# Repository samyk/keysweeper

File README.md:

**KEYSWEEPER // SIGINT // SAMY.PL // REL TO ALL // APPLIED HACKING**

# [KeySweeper](http://samy.pl/keysweeper/)

**[KeySweeper](http://samy.pl/keysweeper)** is a stealthy Arduino-based device, camouflaged as a functioning USB wall charger, that wirelessly and passively sniffs, decrypts, logs and reports back (over GSM) all keystrokes from any Microsoft wireless keyboard in the vicinity.

All keystrokes are logged online and locally. SMS alerts are sent upon trigger words, usernames or URLs, exposing passwords. If unplugged, KeySweeper continues to operate using its internal battery and auto-recharges upon repowering. A web based tool allows live keystroke monitoring.

**Live demonstration** and full details available in the video:

-----

**Point of Contact:** [@SamyKamkar](https://twitter.com/samykamkar) // <code@samy.pl> // <http://samy.pl>

**Released:** January 12, 2015

**Source code / schematic:** [https://github.com/samyk/keysweeper](https://github.com/samyk/keysweeper)

**Unit Cost:** $10 - 80 depending on operation

**Status:** Operational, open source, open hardware, declassified.

-----

# (U) Capabilities

**[KeySweeper](http://samy.pl/keysweeper)** is a stealthy Arduino-based device, camouflaged as a functioning USB wall charger, that wirelessly and passively sniffs, decrypts, logs and reports back all keystrokes from any Microsoft wireless keyboards (which use a proprietary 2.4GHz RF protocol) in the area.

Keystrokes are sent back to the KeySweeper operator over the Internet via an optional GSM chip, or can be stored on a flash chip and delivered wirelessly when a secondary KeySweeper device comes within wireless range of the target KeySweeper. A web based tool allows live keystroke monitoring.

KeySweeper has the capability to send SMS alerts upon certain keystrokes being typed, e.g. "www.bank.com". If KeySweeper is removed from AC power, it appears to shut off, however it continues to operate covertly using an internal battery that is automatically recharged upon reconnecting to AC power.

KeySweeper extends the work of Travis Goodspeed on the [goodfet.nrf](http://travisgoodspeed.blogspot.co.uk/2011/02/promiscuity-is-nrf24l01s-duty.html) project and of Thorsten Schröder and Max Moser of the [KeyKeriki v2.0](http://www.remote-exploit.org/?page_id=602) project.

-----

# (U) Hardware

### Arduino / Teensy microcontroller
**$3 - 30**: An [Arduino](http://arduino.cc/en/Main/ArduinoBoardProMini) or [Teensy](https://www.pjrc.com/teensy/) microcontroller can be used. In my build, I use an 3.3v Arduino Pro Mini due to its very thin profile.

### nRF24L01+ 2.4GHz RF Chip
**$1**: I use a $1 nRF24L01+ RF chip which communicates using GFSK over 2.4GHz. More details are available below, and these chips can be purchased for as low as $1 on eBay. These chips can only communicate using proprietary protocols, and are not meant for sniffing, however we will see below they can be used in clever ways to promiscuously sniff.

### AC USB Charger
**$6**: I use an inexpensive [AC USB charger](https://www.adafruit.com/products/501) (rectifier) which converts AC power to 5v DC, and this one I link to happens to have a screw which makes it easy to open (I've destroyed a few others in the process of opening). If using the GSM version of KeySweeper, I actually use two USB chargers -- the internals of a small charger (similar to that of an iPhone charger), and the external case from a larger USB charger.

### SPI Serial Flash Chip
**OPTIONAL ($2)**: An optional [SPI Serial Flash chip](https://www.adafruit.com/product/1564) can be used to store keystrokes on. If you use the FONA GSM board below, this is not necessary as keystrokes can be stored through the internet live, however if you wish to have a lower cost option, you can store keystrokes onto this chip within KeySweeper, and obtain the keystrokes later by getting within 2.4GHz wireless range of the device with a secondary device which will siphon the keystrokes from it.

Most microcontrollers have very limited memory or EEPROM to store data on, thus the advantage of having a flash chip to store these keystrokes on.

### Adafruit FONA
**OPTIONAL ($45)**: Adafruit has created a board called the [FONA](https://www.adafruit.com/products/1963) which allows you to use a 2G SIM card to send/receive SMS's, phone calls, and use the Internet directly from the device.

Using this, no flash chip is necessary as keystrokes are immediately sent to a backend server for proper data collection. Additionally, if specific keywords are ever typed by the target keyboards, an SMS message can be sent to a specified number to alert the operative of the fact.

### SIM Card
**OPTIONAL ($3, only if using FONA)**: The FONA requires a mini-SIM card (not a micro-SIM). I use a T-Mobile prepaid SIM card. I suggest use of T-Mobile as they support 2G, where most other carriers have or are deprecating their 2G network, and the FONA only supports 2G for Internet. Make sure you get the right size of SIM card -- more details on [FONA SIM requirements here](https://learn.adafruit.com/adafruit-fona-mini-gsm-gprs-cellular-phone-module/obtaining-a-sim).

### 3.7V Lithium-Ion (LiOn or LiPo) Battery
**OPTIONAL ($5 and up, only if using FONA)**: The FONA provides on-board LiPo/LiOn battery recharging, and while KeySweeper is connected to AC power, the battery will be kept charged, but is required nonetheless. Additionally, KeySweeper continues to operate covertly from battery power when pulled from AC power, and begins to recharge upon reconnecting to AC power.

-----

# (U) Software

### KeySweeper
KeySweeper's source code can be obtained in entirety from my github: <https://github.com/samyk/keysweeper>

There are multiple parts to KeySweeper. The primary code is installed on the microcontroller, while a web based backend using [jQuery](http://jquery.com/) and [PHP](http://php.net/) logs all keystrokes and provides a web interface for live monitoring of the target keyboards.

KeySweeper also needs the following files from [maniacbug's RF24 library](https://github.com/maniacbug/RF24):
* `RF24.h`
* `nRF24L01.h`
* `RF24_config.h`

Just copy the files into the `keysweeper_mcu_src` directory. You also have to change the `#include` statement in the `RF24.h` file from `#include <RF24_config.h>` to `#include "RF24_config.h"`.
 
### Adafruit FONA library
You should use [my version of the Adafruit FONA library](https://github.com/samyk/Adafruit_FONA_Library) as I include an additional option that allows the FONA to let us know when there's a new text message. In the original library, you must constantly poll to see if there are more text messages than you expect, however with my version you can enable an option `fona.setSMSInterrupt(1)` which causes the RI (Ring Interrupt) pin to pull low for a moment upon new SMS messages.

### jQuery Terminal
I've created a backend tool that allows you to monitor keyboards live through a web page. The [jQuery Terminal](http://terminal.jcubic.pl/) plugin makes it look cooler.

### jQuery UI Virtual Keyboard
[jQuery UI Virtual Keyboard](https://github.com/Mottie/Keyboard) continues to make the KeySweeper live spy interface tool look cool, showing keys on the virtual keyboard get pressed when the user actually presses keys.

-----

# (U) Determining Keyboard Wireless Protocol

Upon obtaining a Microsoft wireless keyboard, if it's in our possession, we can refer to the back to inspect the FCC ID. On my keyboard, the FCC ID (which is required by all devices using radio frequencies in the US) is **C3K1455**, which we can easily search on the [FCC's website](http://fccid.net/number.php?fcc=C3K1455&id=451957#axzz3NptwlcmB).

Immediately we discover the keyboard communicates on **2403 - 2480MHz** based on the [FCC report](http://fccid.net/number.php?fcc=C3K1455&id=451957#axzz3NptwlcmB).

Now that I know this is a 2.4GHz device, I assume it's either operating using a common 2.4GHz protocol such as wi-fi, bluetooth, zigbee, or others, or it's operating using a proprietary protocol. Due to the fact that the device came with its own USB dongle (with its own [FCC ID, C3K1461](http://fccid.net/number.php?fcc=C3K1461&id=247815#axzz3NptwlcmB)), it's more than likely a proprietary 2.4GHz signal.

Because it's likely proprietary 2.4GHz, we need to now use some method of 2.4GHz sniffing. Wifi sniffers will not help as this isn't 802.11 (such as what we used in [SkyJack](http://samy.pl/skyjack/)), and RTL-SDR by itself won't help as it caps out around 2.2GHz unless additionally using an RF down converter (we used RTL-SDR in [Digital Ding Dong Ditch](http://samy.pl/dingdong/)), so I immediately want to use [HackRF](https://greatscottgadgets.com/hackrf/), a powerful and inexpensive software defined radio, however while it's extremely powerful for its price, we may be able to get away with more inexpensive hardware.

Based off previous experience, my assumption is the keyboard is using something like a [Nordic nRF24L01+](https://www.nordicsemi.com/eng/Products/2.4GHz-RF/nRF24L01P), a [TI CC2500](http://www.ti.com/product/cc2500), or [Cypress CYRF6936](http://www.cypress.com/?rID=14284), but we won't know for sure without further inspection.

After pulling the screws from the keyboard and opening it up, we see a single chip responsible for everything. It's labeled **NRF 24LE1H**, which sounds a lot like nRF24L01 (n=[Nordic Semiconductor](https://www.nordicsemi.com/), RF=Radio Frequency, 24=2.4GHz)! We quickly find the [nRF24LE1](http://www.nordicsemi.com/eng/Products/2.4GHz-RF/nRF24LE1) chip with a search and see that it in fact has the nRF24L01+ RF chip integrated with a CPU (System-on-Chip/SoC), and a quick search on eBay shows the nRF24L01+ can be shipped to us for under $1.

	The nRF24LE1 integrates an nRF24L01+ 2.4GHz RF transceiver core, enhanced 16MHz 8-bit 8051 compatible CPU, 1kB + 256B RAM, 16kB embedded Flash, and a wide range of system peripherals

Looking at the [nRF24L01+ datasheet](https://www.sparkfun.com/datasheets/Components/SMD/nRF24L01Pluss_Preliminary_Product_Specification_v1_0.pdf), we see this is a 2.4GHz RF chip that operates at either 250kbps/1Mbps/2Mbps, uses GFSK ([Gaussian frequency-shift keying modulation](http://en.wikipedia.org/wiki/Gaussian_frequency-shift_keying) is a digital frequency modulation/FM), and unfortunately lacks any legitimate promiscuous or direct mode for sniffing...or does it?

-----

# (U) Sniffing Proprietary 2.4GHz Signals

While I would normally pull out something like a HackRF or RTL-SDR with digital down converter (to get 2.4GHz into RTL-SDR range), it would be really nice if we could sniff with more inexpensive hardware, as ultimately I want to package everything up into a device that can be left in the field.

After a basic search, an amazing page came up from [Travis Goodspeed](http://travisgoodspeed.blogspot.com/2011/02/promiscuity-is-nrf24l01s-duty.html), where he not only sniffs a similar keyboard (Microsoft Comfort Desktop 5000), but he also demonstrates how to turn the nRF24L01+ into a 2.4GHz sniffer using his [GoodFET](http://goodfet.sourceforge.net/) device, and a host computer with the [goodfet.nrf](http://goodfet.sourceforge.net/clients/goodfetnrf/) python application.

Travis found that sniffing with the device is traditionally difficult because not only must you specify the channel (frequency) to listen to, you must specify a MAC address to listen on. The nRF chip will only deliver packets sent to that specific MAC address. Additionally, the nRF chip  won't tell you the MAC address since you already specified it (it's assumed to be in one of our `RX_ADDR_P[0-5]` pipes, found in the datasheet.)

However when specifying the length of the MAC, Travis found there is one option which is considered "illegal" in the datasheet (`SETUP_AW, 0x03 set to 00`), but actually sets the MAC to 2 bytes! Also, by setting the MAC to data that would typically be found in the preamble (`0x00AA or 0x0055, in binary 0000000010101010 or 0000000001010101`), we can fool the device into giving us the packet early, providing a full MAC address to us in the data portion! Read his [great write-up](http://travisgoodspeed.blogspot.com/2011/02/promiscuity-is-nrf24l01s-duty.html) for all the details.

-----

# (U) Increasing Speed and Portability

Now while we can use a GoodFET, computer and nRF24L01+ for sniffing during testing, we ultimately want this to be on an inexpensive and embedded device. We can take some of Travis' great work in Python and port it over to embedded C so that we can load it onto a microcontroller rather than requiring a computer+GoodFET.

Additionally, we implement a few improvements. Goodfet.nrf provides a method of scanning for devices by performing the following:

* start at frequency 2400MHz
* set datarate to 1Mbps and MAC to 0x00AA, listen for 10 seconds
* set datarate to 2Mbps and MAC to 0x00AA, listen for 10 seconds
* set datarate to 1Mbps and MAC to 0x0055, listen for 10 seconds
* set datarate to 2Mbps and MAC to 0x0055, listen for 10 seconds
* increment frequency and start over, and once we hit 2528MHz, reset to 2400 (128 frequencies)
* upon seeing a potential keyboard, we require at least four packets to meet a threshold to be sure it's a legitimate packet as get many false positives

This means to scan the full range of frequencies, it takes ~85 minutes and at least several keystrokes must be pressed while we're sniffing within the correct 10 second period. After going over Travis' research and keyboard, the [KeyKeriki](http://www.remote-exploit.org/articles/keykeriki_v2_0__8211_2_4ghz/) research and keyboard, and my own keyboard, we can implement a few improvements:

* if you recall from the FCC, we're only using 2403 - 2480MHz for these keyboards, reducing our 128 possible frequencies down to 78 (about 40% reduction in scanning)
* all keyboards use 2Mbps, cutting our search in half
* after inspecting more keyboards, I found that all Microsoft keyboards begin with 0xCD as the MAC, which tells us that our preamble will always be `0xAA (10101010)` because the preamble of 0xAA is always followed by a 1 bit (`0xCD is 11001101`) in order to keep the bits alternating, cutting our search in half
* because we know the first byte of our MAC (0xCD), and we also know certain packets to look for, we simply detect only those packets which means we only ever need to see a single packet to be confident that it is in fact a keyboard
* we reduce the scan per frequency to 500ms, causing our scan to take under 40 seconds to complete one full sweep

-----

# (U) Decrypting Keystrokes

Thorsten Schröder and Max Moser presented a great device, the [KeyKeriki](http://www.remote-exploit.org/articles/keykeriki_v2_0__8211_2_4ghz/), capable of sniffing Microsoft keyboards and have fully reverse engineered the decryption process and produced a device for doing so. However Travis points out that their device requires two radios and a high-end microcontroller to capture and parse packets at the 2Mbps speed the keyboards communicate at. Travis' project is great as well, however requires a host computer and will be too large for our covert implementation. We improve upon these designs in this scenario by requiring only an inexpensive radio and microcontroller, both low power and very small, no computer or fancy radios required.

Thorsten and Max discovered the keystrokes are simply encrypted (xor'd) with the MAC address in [ECB mode](http://en.wikipedia.org/wiki/Block_cipher_mode_of_operation#Electronic_codebook_.28ECB.29), which we are able to sniff after using Travis' method of abusing the nRF24L01+ to both sniff and reveal MAC addresses. This "encryption" is the equivalent of taking a deck of cards, cutting it once, and calling it shuffled. 

After further investigation, I found that since we now know all Microsoft keyboards begin with 0xCD as the MAC address, the actual keystroke (in orange below) happens to be aligned with the first byte of the MAC address (0xCD). This means **even if we do not know the MAC address, we can decrypt the keystroke**, as the alignment will never change, and 0xCD is always the first byte of the MAC.

An additional discovery is that since the length of the encryption portion of the packet is 11 bytes, the MAC is 5 bytes, and the CRC is each byte xor'd with another (before encryption), something interesting happens. Since the MAC is xor'd twice, we can also calculate the checksum without knowing the MAC address. This is because the MAC address is in there in full twice, and xoring any number by itself (or xor the MAC with the MAC) cancels itself out. The 11th byte is the first byte of the MAC again, which we always know is 0xCD. This allows us to perform other attacks, such as altering the keystroke and CRC, again without knowing the MAC address. I will present this and some other fun demonstrations in a future project.

A page from the KeyKeriki presentation demonstrates the decryption process:

* Device type 0x0A = keyboard, 0x08 = mouse
* Packet type 0x78 = keystroke, 0x38 = idle (key is held down)
* Model type 0x06 = keyboard? This is the same HID code for a keyboard
* HID code 0x05 = letter 'b' (described in section 7 [here](http://www.freebsddiary.org/APC/usb_hid_usages.php))

Our decryption method, implemented in the KeySweeper source code:

```
// decrypt those keyboard packets!
void decrypt(uint8_t* pkt)
{
  // our encryption key is the 5-byte MAC address and
  // starts 4 bytes in (4-byte header is unencrypted)
  for (int i = 4; i < 15; i++)
    pkt[i] ^= mac >> (((i - 4) % 5) * 8) & 0xFF;
}
```

-----

# (U) Building / Usurping a USB Charger

**WARNING: Devices which connect to AC mains are using high-voltage power, and the device we are creating which connects to AC is not safe, nor does it meet typical electrical safety standards. This is a dangerous device and if used or built improperly, can kill, cause fire, or other severe damage. Do not build an AC-powered device unless you know what you're doing. If you wish to continue building this device but without AC power, simply use a battery or power the device from USB directly to safely follow along.**

KeySweeper uses extremely low-power and low profile hardware to remain as covert as possible. KeySweeper can be operated from a battery, or from ~3-20V DC power. Because we wish to keep KeySweeper powered at all times, we stealthily install it inside of an innocent wall USB charger which we expect to be always plugged in.

In the case that the USB charger is unplugged, KeySweeper stealthily continues its operation using its (optional) internal battery. The moment KeySweeper is plugged back in, it switches back over to using AC power, and simultaneously recharges the battery.

If you are simply building KeySweeper **without** the GSM board, you can fit everything in a typical AC USB wall charger. I suggest looking for one that has a screw holding it together, as most others are sealed shut and requires destruction of some part of the device in order to open it.

If you decide to use the GSM board, I found it would not fit in this type of USB charger along with the rest of the electronics. However, I discovered that by opening a smaller USB charger (similar to the iPhone USB chargers), we find a much smaller rectifier (AC->DC) and step-down convertor (high voltage->5V) that allows **all** of our electronics to fit into the larger USB charger. 

My friend Dana lent me her doll soldering iron. I don't quite understand what she uses it for, but it's a soldering iron with an attachable razor. This is great for cutting through plastic, and dolls, I presume. She took the iron back as soon as I explained what the device would do. Apparently she does not support this, though I'm not sure why. I'm sure I'll find out after I sniff more keystrokes from her keyboard.

**WARNING: Again, because we are dealing with AC power, this is very dangerous. Do not open/rewire an AC powered device unless you know what you're doing.** You can still build KeySweeper by simply powering everything from a USB charger, port or battery without modifying an AC-based device.

It's also important to wire up our Arduino via the RAW port to the 5v USB power with correct polarity (negative to GND, positive to RAW). In this case, I'm using a 3.3v Arduino Pro Mini. The RAW port takes in unregulated voltage between 3.35-12v and uses an onboard voltage regulator to bring it down to 3.3v. Note that our nRF24L01+ chip requires 1.9-3.6v, so giving it 5v is **too much!** Additionally, if you're using an SPI chip such as the [SST25VF016B](http://ww1.microchip.com/downloads/en/DeviceDoc/S71271_04.pdf), it requires 2.7-3.6v, so again using 5v is **too much!** Be sure to use the regulated 3.3v off of the Arduino (from the VCC pin on a 3.3v Arduino, or the 3V3 pin on a 5v Arduino.) 

*note: the USB board pictured next to the multimeter is the original before I had decided to swap it out with a smaller one to fit in the GSM board as well*

After grabbing all of our hardware, we can see it all fits with space in our charger (before wiring):

For fun, I tied the charger's LED to pin 6 on the Arduino and while the LED appears to behave the same, I actually have it flash upon sniffing keystrokes. This will likely blow your cover, but is really fun to watch. I also ensure the LED turns off when power to AC is lost, even if the rest of the device continues to operate from the internal battery.

We also want to make sure we leave the rest of the USB charger operational so that other devices can continue to get power from the USB charger.

-----

# (U) Optional Secondary KeySweeper
If you wish to forgo the GSM board to keep costs down, you can create a secondary KeySweeper device simply containing an Arduino and nRF24L01+. While compiling the secondary one, uncomment the `#define BACKTRACER 1`.

The way this works is if the secondary KeySweeper (BACKTRACER) ever comes within wireless distance (using the 2.4GHz nRF24L01+) of the first one, it auto-detects the existence of the first one and the initial KeySweeper device will dump its logs to the BACKTRACER. Autodetection is built into both KeySweepers so they can quickly find each other, thanks to the ability of the nRF24L01+ to have multiple RX pipes.

If you have the BACKTRACER hooked up to a computer, the keylogs will be dumped to serial, and you can send an 'E' command over serial to erase the contents of the original KeySweeper's SPI Flash chip now that you've obtained its contents. You can walk away allowing the original KeySweeper to continue logging keystrokes.

-----

# (U) Schematic

Click for larger version (FONA-based schematic), or [click here](http://samy.pl/keysweeper/keysweeper.fzz) for the Fritzing file.

-----

# (U) Contact

**Point of Contact:** [@SamyKamkar](https://twitter.com/samykamkar)

You can see more of my projects at <http://samy.pl> or contact me at <code@samy.pl>.

------

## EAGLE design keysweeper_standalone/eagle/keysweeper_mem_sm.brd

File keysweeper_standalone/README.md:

Keysweeper Modifications

Originally, Samy.PL created and documented the keysweeper ( [https://samy.pl/keysweeper/)](https://samy.pl/keysweeper/)) as a tool to man in the middle vulnerable Microsoft wireless keyboards.

His original design used a Arduino Mini, GSM module, 2.4 GHz System on a Chip (SoC) and USB Charger to lock onto a channel used by a Vulnerable MS wireless keyboard, capture the keystrokes and post them to a web site where the attacker could use the information.

After reviewing the design, it was determined that using the device could inject risk that a third party could ease drop on the data stream or gain access to the web application.  So modifications were designed to capture the keystrokes and log them to an on board memory chip that could be reviewed at a later time.  Additionally, a battery was added so that the device could be carried in a pocket, backpack or left taped under a desk, without need of plugging into a 120 volt wall socket.

Samy.Pl page mentions that the W25Q80BV flash chip can be used, but didn&#39;t contain code to use it.  To make these changes a library had to be developed to interface with the chip.  This library provides methods to read, write and clear the contents of the chip from an Arduino project.  It provides both a programmatic API and a user prompt that allows the same capabilities.

https://github.com/osok/WinBod-25Q80BV

The W25Q80BV chip

A daughter board was designed in Eagle CAD, and fabricated by OSH Park, which connected the W25Q80BV chip to the Arduino mini and NRF24L01.  Surface mount components were used to make the board lower smaller.

The eagle cad designs, including the .brd file which is used when uploading to OSHPark for board fabrication, can be found in the eagle directory.

The board is 2 inches in length.

The NRF24L01 board extends off the end of the board to provide less interference with the antenna.  The Arduino Mini is coupled to the daughter board with riser pins.

All the boards attached

The battery that I choose was a 3.7 volt LiPo for small drones.

Finally, some shrink wrap allows a neat little package.

The most recent rev of the board has an on off power switch and a switch for keyboard hijacking and reading the memory.  Switch it to memory read then connect to the Arduinos serial interface with a FTDI connector and interact with the memory app.

To have the board fabricated, upload the design to OSH Park.  You will need to order 3 boards minimum, which will cost around $10 and take 2 to 3 weeks to arrive.   [https://oshpark.com/](https://oshpark.com/)  The board is Open source Hardware.

To have a stencil created for spreading solder paste you can upload the .brd file to OSH Stencil.  https://www.oshstencils.com/

The updated code for the Arduino can be downloaded from my GitHub.
https://github.com/osok

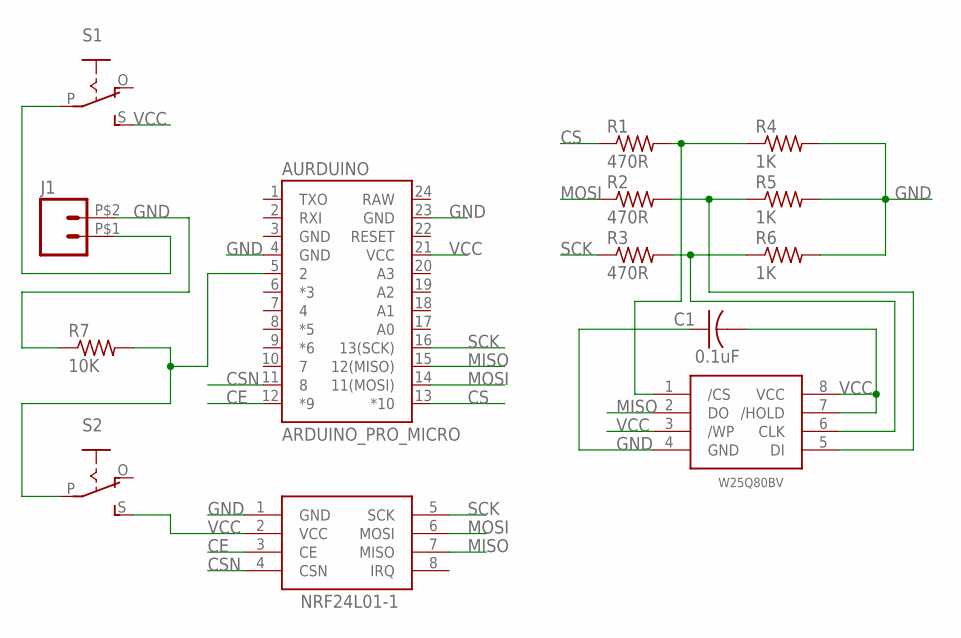
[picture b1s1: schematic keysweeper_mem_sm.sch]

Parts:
AURDUINO: ARDUINO_PRO_MICRO
C1: 0.1uF; C0805K
J1: M02PTH2; 1X02_BIG
R1, R2, R3: 470R; R0805W
R4, R5, R6: 1K; R0805W
R7: 10K; R0805W
S1, S2: EG1218S; EG1218
U1: NRF24L01-8PIN; NRF24L01
U2: W25Q80BV-SMD

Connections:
CE: AURDUINO.12 (*9), U1.3 (CE)
CS: AURDUINO.13 (*10), R1.1
CSN: AURDUINO.11 (8), U1.4 (CSN)
GND: AURDUINO.4 (GND), AURDUINO.23 (GND), C1.1, J1.P$2 (2), R4.2, R5.2, R6.2, R7.1, U1.1 (GND), U2.4 (GND)
MISO: AURDUINO.15 (12(MISO)), U1.7 (MISO), U2.2 (DO)
MOSI: AURDUINO.14 (11(MOSI)), R2.1, U1.6 (MOSI)
unnamed: R1.2, R4.1, U2.1 (/CS)
unnamed: R2.2, R5.1, U2.5 (DI)
unnamed: R3.2, R6.1, U2.6 (CLK)
unnamed: AURDUINO.5 (2), R7.2, S2.P
unnamed: J1.P$1 (1), S1.P
SCK: AURDUINO.16 (13(SCK)), R3.1, U1.5 (SCK)
VCC: AURDUINO.21 (VCC), C1.2, S1.S, S2.S, U1.2 (VCC), U2.3 (/WP), U2.7 (/HOLD), U2.8 (VCC)

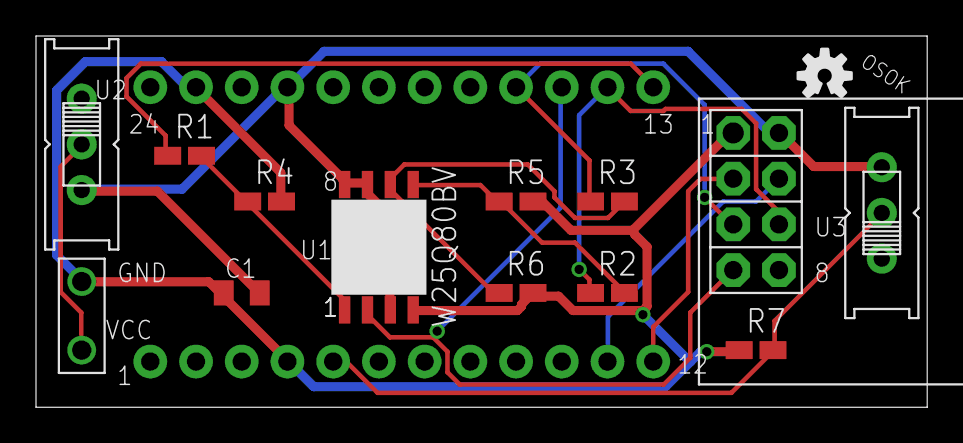
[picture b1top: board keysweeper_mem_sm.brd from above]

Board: 2 copper layers, 49.5 x 20.6 mm, 15 parts (0 on the bottom side), 13 nets.

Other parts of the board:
U$2: OSHW-LOGO-S

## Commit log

2015-01-12 First release of KeySweeper
2015-01-12 added SMS image
2015-01-12 added video
2015-01-12 small update
2015-02-24 keysweeper_mcu_src.ino
2015-02-24 updated printing of packets to serial
2015-03-19 Update keysweeper_mcu_src.ino
    Fixed sms sending
2015-03-20 Update keysweeper_mcu_src.ino
    Fixed triggers not working after being triggered once.
    Fixed a false trigger if stackptr was reset to zero once it was larger than the size of the stack.
2017-01-20 Initial Check in
2017-01-20 Initial Checkin
2017-01-20 initial checkin
    added photos
2017-02-22 updated content
2017-02-22 test

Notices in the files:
parts and their libraries:
SparkFun-Boards: Licensing: Creative Commons ShareAlike 4.0 International - https://creativecommons.org/licenses/by-sa/4.0
